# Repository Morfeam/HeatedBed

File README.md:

# HeatedBed
The code, circuit, and 3d models used in the creation of a module to control my DIY 3d printers heated bed temperature.

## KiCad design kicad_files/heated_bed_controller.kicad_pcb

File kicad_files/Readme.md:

# Heated Bed Controller - KiCad Files and Circuit Diagrm

### Circuit Diagram (Schematic):

### PCB Layout:

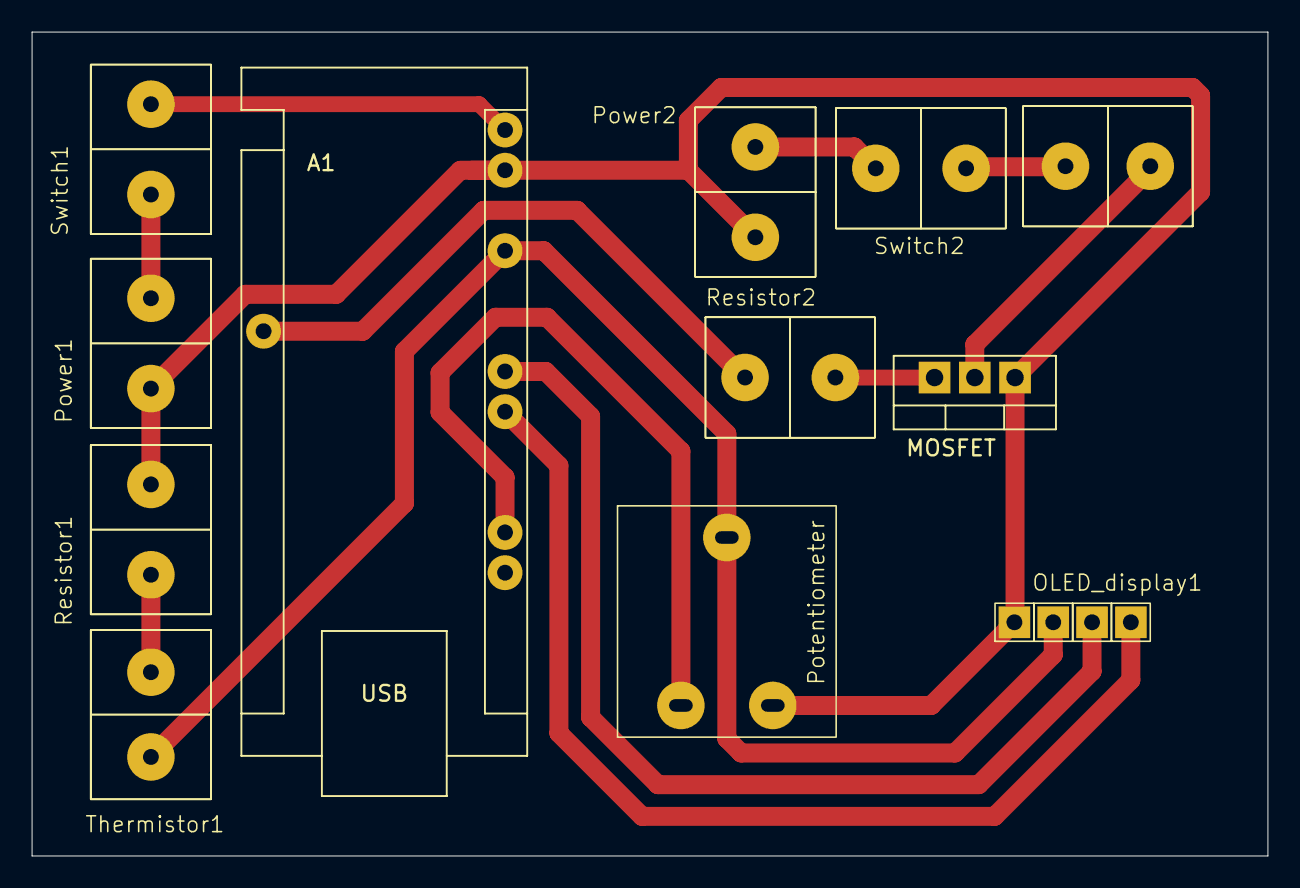
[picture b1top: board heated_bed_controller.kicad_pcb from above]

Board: 2 copper layers, 78.0 x 52.0 mm, 12 parts (0 on the bottom side), 12 nets.

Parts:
A1: Arduino_Nano_v3.x; Arduino_Nano
MOSFET: IRF3205; TO-220-3_Vertical
OLED_display1: OLED_display
Potentiometer: R_Potentiometer; arduino_kit_potentiometer
Power1: 12v; screw_mount
Power2: 24v; screw_mount
R2: Heated Bed; screw_mount
Resistor1: 10K; screw_mount
Resistor2: 330R; screw_mount
Switch1, Switch2: SW_SPST; screw_mount
Thermistor1: Thermistor; screw_mount

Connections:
unnamed: A1.27 (+5V), OLED_display1.2 (VCC), Potentiometer.1, Thermistor1.1
unnamed: Resistor1.1, Thermistor1.2
unnamed: A1.23 (A4), OLED_display1.4 (SDA)
unnamed: A1.24 (A5), OLED_display1.3 (SCL)
unnamed: A1.6 (D3), Resistor2.1
unnamed: A1.30 (VIN), Switch1.2 (B)
unnamed: MOSFET.2 (D), R2.1
unnamed: A1.29 (GND), MOSFET.1 (G), OLED_display1.1 (GND), Potentiometer.3, Power1.2 (-), Power2.2 (-), Resistor1.2
unnamed: MOSFET.3 (S), Resistor2.2
unnamed: Power1.1 (+), Switch1.1 (A)
unnamed: Power2.1 (+), Switch2.1 (A)
unnamed: R2.2, Switch2.2 (B)

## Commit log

2025-07-04 migrate local heated bed project to repo in github
2025-07-04 add local heated bed project files
2025-07-05 add markdown and delete test folde
2025-07-05 Adds Kicad, 3d models, and documentation
2025-07-05 Making readme cleaner
2025-07-05 making jpg lowercase?
2025-07-09 correcting resistance in docs
